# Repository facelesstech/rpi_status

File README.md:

# rpi_status
a ssd1306 oled screen with a ws2812 8 led ring and a bmp180 temp sensor. Also added shutdown button and reset button

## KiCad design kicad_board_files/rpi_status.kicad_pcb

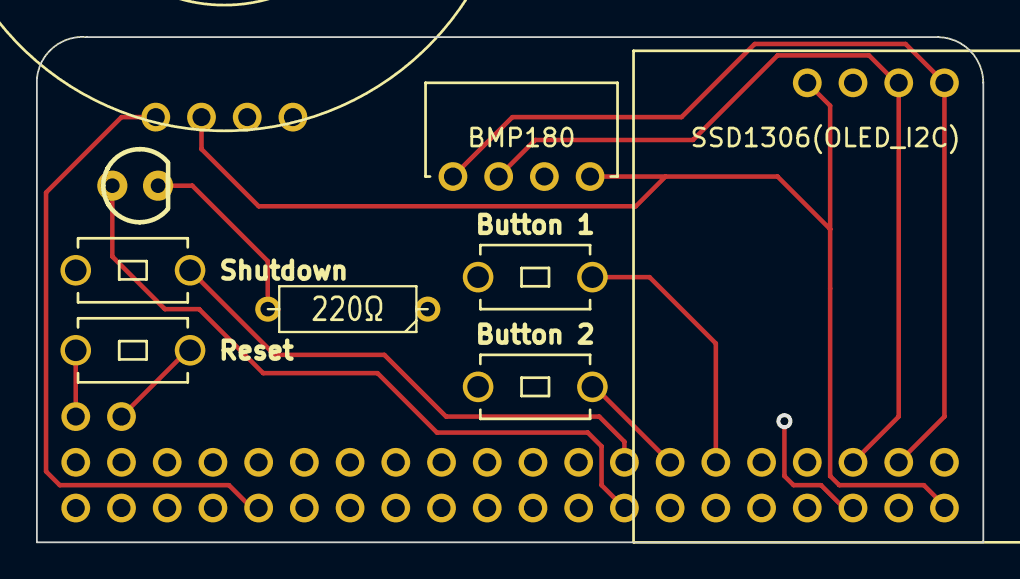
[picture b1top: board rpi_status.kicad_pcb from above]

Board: 2 copper layers, 52.6 x 28.1 mm, 11 parts (0 on the bottom side), 12 nets.

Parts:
220Ω: R; R3-5
D1: LED; led_3mm_custom
SW1, SW2, SW3, SW4: SW_PUSH; button_single_custom
U1: SSD1306(OLED_I2C); ssd1306_oled_screen
U2: BMP180
U3: WS2812_RING; ws2812_ring_custom
U4: RASPBERRY_PI_HEADER; raspberry_pi_GPIO_header
VAL: OSH_final_silks_back

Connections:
unnamed: D1.1, U4.16
unnamed: SW2.2, U4.13
unnamed: SW4.2, U4.42
unnamed: U3.1, U4.32
unnamed: SW4.1, U4.41
unnamed: U1.3, U2.2, U4.5
unnamed: SW3.2, U4.15
unnamed: U1.4, U2.1, U4.3
unnamed: 220Ω.1, SW1.1, SW2.1, SW3.1, U1.2, U2.3, U3.3, U4.6
unnamed: SW1.2, U4.11
unnamed: U1.1, U2.4, U3.2, U4.2
unnamed: 220Ω.2, D1.2

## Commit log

2016-02-18 Gerber files for the board
2016-02-18 Shutdown scrip with pull up resistor
2016-02-18 fixed README file
2016-02-18 pull up shutdown python script
2016-02-22 moved files into new folder
2016-02-22 removed folder
2016-02-22 basic temp loggin with thingspeak.com
2016-02-22 weather screen for wheezy build
2016-02-25 change folder name
2016-02-25 change file name
2016-02-25 display weather on the status screen
2016-02-25 display weather on status screen
2016-02-29 added jessie temp logger code
2016-02-29 removed file
2016-03-05 changed ws2812 code to the write colour for aqur
2016-03-05 bug fix for aqur colour on ws2812
2016-03-07 wheezy version of the templogger with readme
2016-03-08 Added code to light ring up as the temp goes up
2016-03-12 fixed the scalling used for the ws2812 ring
2016-03-13 fixed readme install instructions
2016-05-08 fixed the orange colour of the ws2812 led
2016-09-24 Added board files
2016-10-06 changed the colour values for the new ws2812 library
2016-10-07 turned the ws2812 brightness down
2018-06-10 example code to get ws2812 running
